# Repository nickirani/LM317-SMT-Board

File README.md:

# LM317-SMT-Board
Simple LM317 Board files and BOM
Feel free to use these files and make your own.

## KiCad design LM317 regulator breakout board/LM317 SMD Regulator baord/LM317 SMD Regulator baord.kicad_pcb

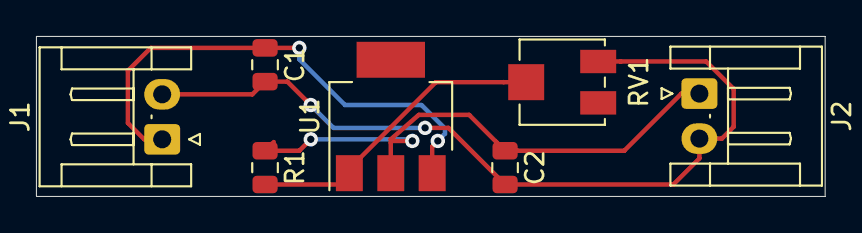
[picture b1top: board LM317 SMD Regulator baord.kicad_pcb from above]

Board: 2 copper layers, 43.8 x 8.9 mm, 7 parts (0 on the bottom side), 4 nets.

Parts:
C1, C2: CP; C_0805_2012Metric
J1, J2: Conn_01x02_Male; JST_EH_S2B-EH_1x02_P2.50mm_Horizontal
R1: R; R_0805_2012Metric
RV1: R_POT; Potentiometer_Bourns_3314J_Vertical
U1: LM317_3PinPackage; SOT-223

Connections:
GND: C1.2, C2.2, J1.2, J2.2, RV1.3
unnamed: C1.1, J1.1, U1.3
unnamed: C2.1, J2.1, R1.1, U1.2
unnamed: R1.2, RV1.2, U1.1
